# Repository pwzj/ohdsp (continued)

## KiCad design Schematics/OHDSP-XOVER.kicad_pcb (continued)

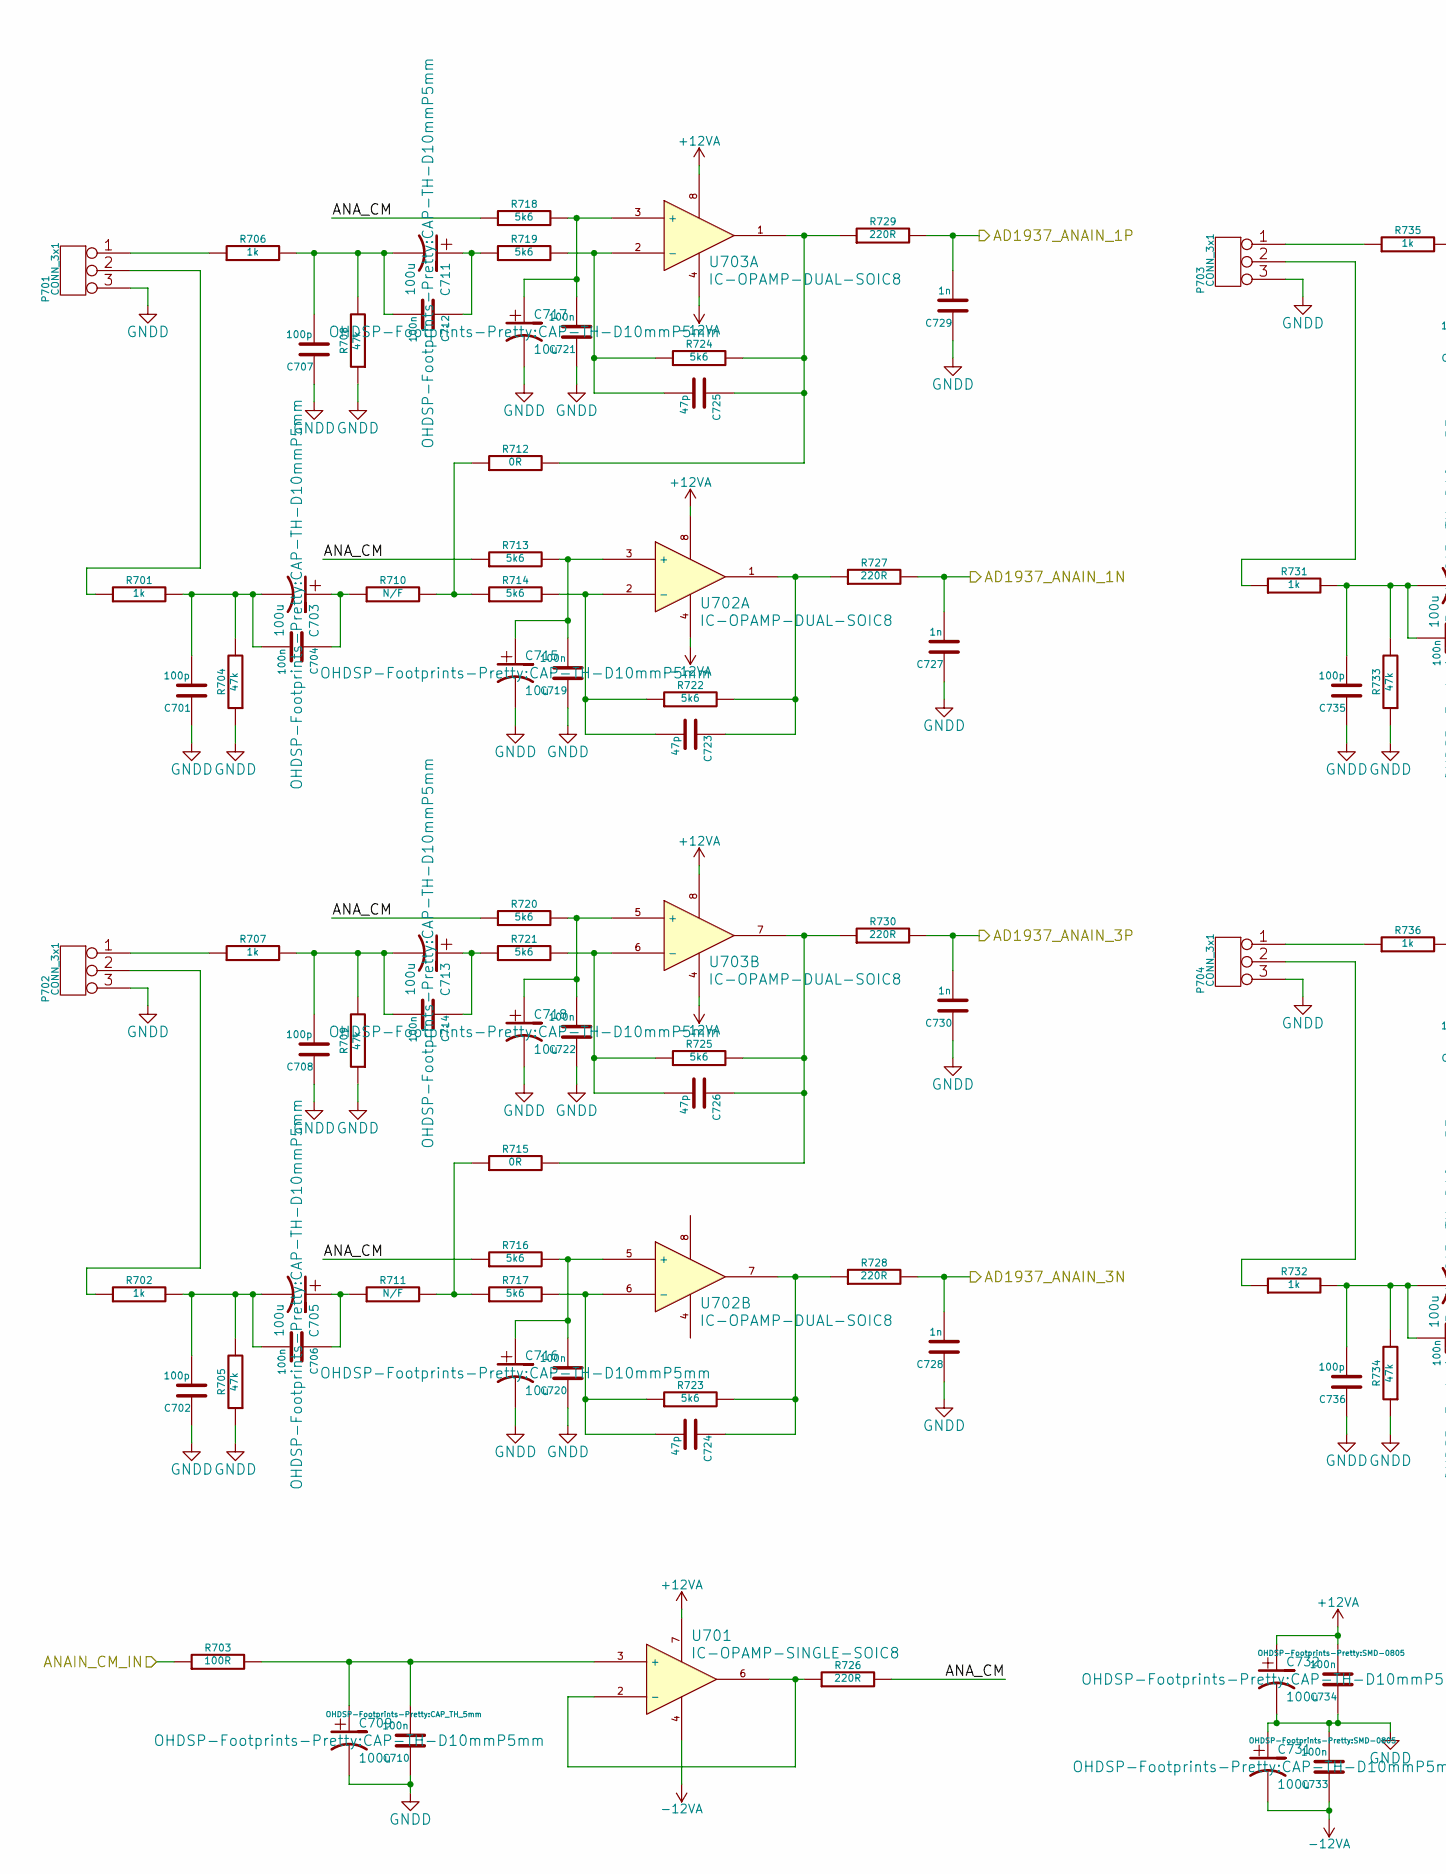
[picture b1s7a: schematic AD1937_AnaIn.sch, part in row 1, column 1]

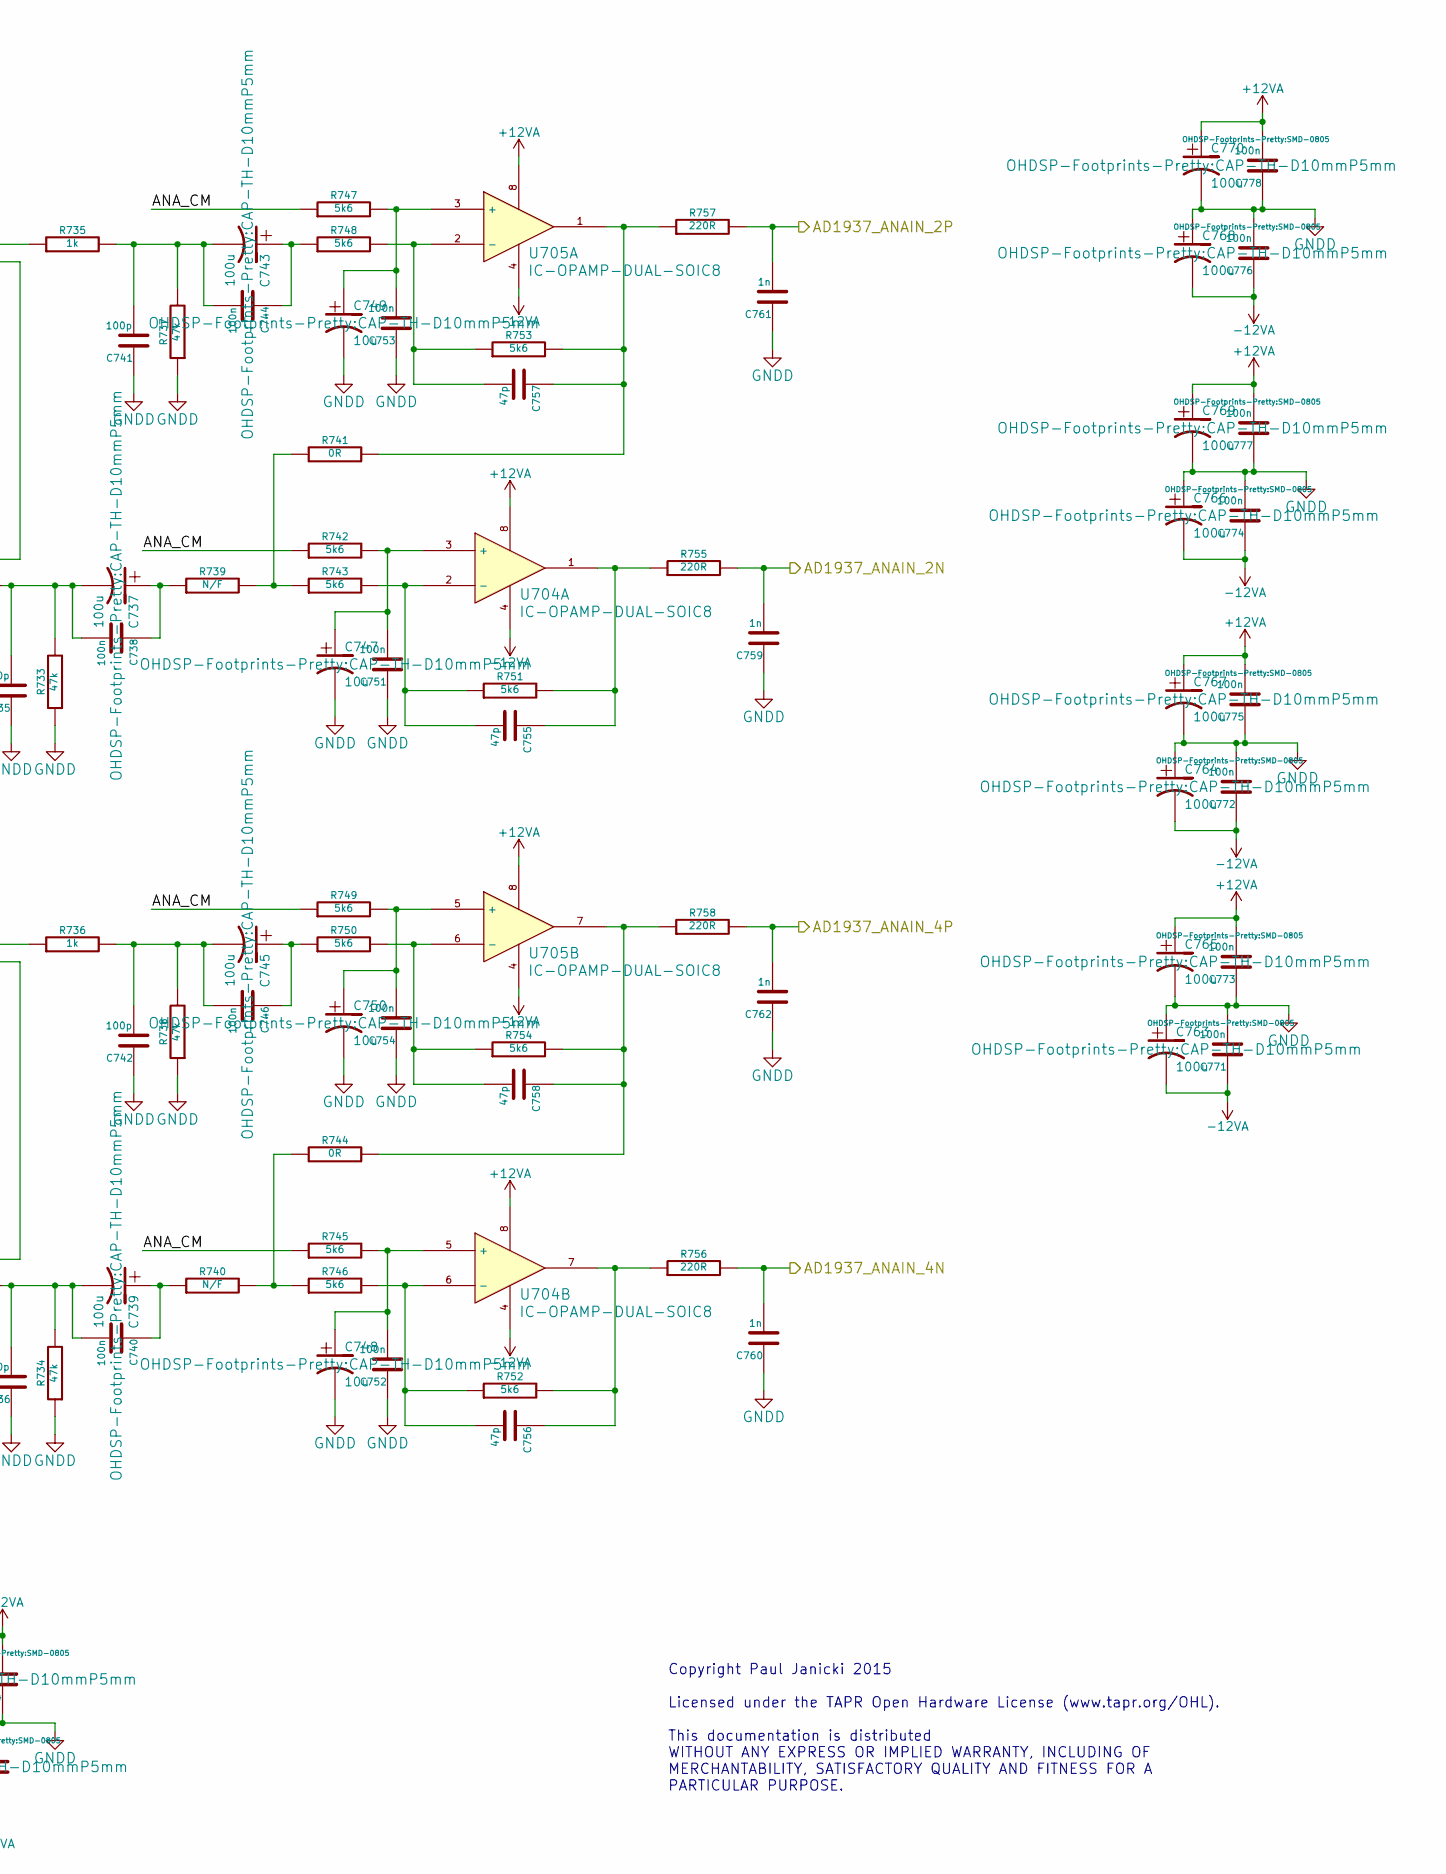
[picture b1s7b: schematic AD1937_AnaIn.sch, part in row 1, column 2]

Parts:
C701, C702, C707, C708, C735, C736, C741, C742: 100p; CAP_TH_5mm
C703, C705, C709, C711, C713, C731, C732, C737, C739, C743, C745, C763, C764, C765, C766, C767, C768, C769, C770: 100u; CAP-TH-D10mmP5mm
C704, C706, C710, C712, C714, C719, C720, C721, C722, C738, C740, C744, C746, C751, C752, C753, C754: 100n; CAP_TH_5mm
C715, C716, C717, C718, C747, C748, C749, C750: 10u; CAP-TH-D10mmP5mm
C723, C724, C725, C726, C755, C756, C757, C758: 47p; CAP_TH_5mm
C727, C728, C729, C730, C759, C760, C761, C762: 1n; CAP_TH_5mm
C733, C734, C771, C772, C773, C774, C775, C776, C777, C778: 100n; SMD-0805
P701, P702, P703, P704: CONN_3x1; CONN_SIL_3
R701, R702, R706, R707, R731, R732, R735, R736: 1k; TH-RES-0W25
R703: 100R; TH-RES-0W25
R704, R705, R708, R709, R733, R734, R737, R738: 47k; TH-RES-0W25
R710, R711, R739, R740: N/F; TH-RES-0W25
R712, R715, R741, R744: 0R; TH-RES-0W25
R713, R714, R716, R717, R718, R719, R720, R721, R722, R723, R724, R725, R742, R743, R745, R746, R747, R748, R749, R750, R751, R752, R753, R754: 5k6; TH-RES-0W25
R726, R727, R728, R729, R730, R755, R756, R757, R758: 220R; TH-RES-0W25
U701: IC-OPAMP-SINGLE-SOIC8; IC_DIP_8
U702, U703, U704, U705: IC-OPAMP-DUAL-SOIC8; IC_DIP_8

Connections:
+12VA: C732.1, C734.2, C765.1, C767.1, C769.1, C770.1, C773.2, C775.2, C777.2, C778.2, U701.7, U702.8, U703.8, U704.8, U705.8; also elsewhere on the board
-12VA: C731.2, C733.1, C763.2, C764.2, C766.2, C768.2, C771.1, C772.1, C774.1, C776.1, U701.4, U702.4, U703.4, U704.4, U705.4; also elsewhere on the board
/AD1937 CODEC/AD1937_CM: R703.1; also elsewhere on the board
/AD1937_AnaIn/AD1937_ANAIN_1N: C727.2, R727.2; also elsewhere on the board
/AD1937_AnaIn/AD1937_ANAIN_1P: C729.2, R729.2; also elsewhere on the board
/AD1937_AnaIn/AD1937_ANAIN_2N: C759.2, R755.2; also elsewhere on the board
/AD1937_AnaIn/AD1937_ANAIN_2P: C761.2, R757.2; also elsewhere on the board
/AD1937_AnaIn/AD1937_ANAIN_3N: C728.2, R728.2; also elsewhere on the board
/AD1937_AnaIn/AD1937_ANAIN_3P: C730.2, R730.2; also elsewhere on the board
/AD1937_AnaIn/AD1937_ANAIN_4N: C760.2, R756.2; also elsewhere on the board
/AD1937_AnaIn/AD1937_ANAIN_4P: C762.2, R758.2; also elsewhere on the board
/AD1937_AnaIn/ANA_CM: R713.1, R716.1, R718.1, R720.1, R726.2, R742.1, R745.1, R747.1, R749.1
GNDD: C701.1, C702.1, C707.1, C708.1, C709.2, C710.1, C715.2, C716.2, C717.2, C718.2, C719.1, C720.1, C721.1, C722.1, C727.1, C728.1, C729.1, C730.1, C731.1, C732.2, C733.2, C734.1, C735.1, C736.1, C741.1, C742.1, C747.2, C748.2, C749.2, C750.2, C751.1, C752.1, C753.1, C754.1, C759.1, C760.1, C761.1, C762.1, C763.1, C764.1, C765.2, C766.1, C767.2, C768.1, C769.2, C770.2, C771.2, C772.2, C773.1, C774.2, C775.1, C776.2, C777.1, C778.1, P701.3, P702.3, P703.3, P704.3, R704.1, R705.1, R708.1, R709.1, R733.1, R734.1, R737.1, R738.1; also elsewhere on the board
unnamed: C701.2, C703.2, C704.2, R701.2, R704.2
unnamed: C702.2, C705.2, C706.2, R702.2, R705.2
unnamed: C703.1, C704.1, R710.1
unnamed: C705.1, C706.1, R711.1
unnamed: C707.2, C711.2, C712.2, R706.2, R708.2
unnamed: C708.2, C713.2, C714.2, R707.2, R709.2
unnamed: C709.1, C710.2, R703.2, U701.3 (+)
unnamed: C711.1, C712.1, R719.1
unnamed: C713.1, C714.1, R721.1
unnamed: C715.1, C719.2, R713.2, U702.3 (+)
unnamed: C716.1, C720.2, R716.2, U702.5 (+)
unnamed: C717.1, C721.2, R718.2, U703.3 (+)
unnamed: C718.1, C722.2, R720.2, U703.5 (+)
unnamed: C723.1, R722.2, R727.1, U702.1
unnamed: C723.2, R714.2, R722.1, U702.2 (-)
unnamed: C724.1, R723.2, R728.1, U702.7
unnamed: C724.2, R717.2, R723.1, U702.6 (-)
unnamed: C725.1, R712.2, R724.2, R729.1, U703.1
unnamed: C725.2, R719.2, R724.1, U703.2 (-)
unnamed: C726.1, R715.2, R725.2, R730.1, U703.7
unnamed: C726.2, R721.2, R725.1, U703.6 (-)
unnamed: C735.2, C737.2, C738.2, R731.2, R733.2
unnamed: C736.2, C739.2, C740.2, R732.2, R734.2
unnamed: C737.1, C738.1, R739.1
unnamed: C739.1, C740.1, R740.1
unnamed: C741.2, C743.2, C744.2, R735.2, R737.2
unnamed: C742.2, C745.2, C746.2, R736.2, R738.2
unnamed: C743.1, C744.1, R748.1
unnamed: C745.1, C746.1, R750.1
unnamed: C747.1, C751.2, R742.2, U704.3 (+)
unnamed: C748.1, C752.2, R745.2, U704.5 (+)
unnamed: C749.1, C753.2, R747.2, U705.3 (+)
unnamed: C750.1, C754.2, R749.2, U705.5 (+)
unnamed: C755.1, R751.2, R755.1, U704.1
unnamed: C755.2, R743.2, R751.1, U704.2 (-)
unnamed: C756.1, R752.2, R756.1, U704.7
unnamed: C756.2, R746.2, R752.1, U704.6 (-)
unnamed: C757.1, R741.2, R753.2, R757.1, U705.1
unnamed: C757.2, R748.2, R753.1, U705.2 (-)
unnamed: C758.1, R744.2, R754.2, R758.1, U705.7
unnamed: C758.2, R750.2, R754.1, U705.6 (-)
unnamed: P701.1, R706.1
unnamed: P701.2, R701.1
unnamed: P702.1, R707.1
unnamed: P702.2, R702.1
unnamed: P703.1, R735.1
unnamed: P703.2, R731.1
unnamed: P704.1, R736.1
unnamed: P704.2, R732.1
unnamed: R710.2, R712.1, R714.1
unnamed: R711.2, R715.1, R717.1
unnamed: R726.1, U701.2 (-), U701.6
unnamed: R739.2, R741.1, R743.1
unnamed: R740.2, R744.1, R746.1

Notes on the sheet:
Copyright Paul Janicki 2015 Licensed under the TAPR Open Hardware License (www.tapr.org/OHL). This documentation is distributed WITHOUT ANY EXPRESS OR IMPLIED WARRANTY, INCLUDING OF MERCHANTABILITY, SATISFACTORY QUALITY AND FITNESS FOR A PARTICULAR PURPOSE.
